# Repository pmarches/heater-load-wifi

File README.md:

What is this?
---

This repository contains code, drawings and schematics for a device that controls a heating element. This device will throttle the AC current of a device to the duty ratio configured via Wifi. 

The device has features that I could not find in commercial devices;

- Wifi connectivity, for both monitoring and control
- Victron Energy compatible drivers
- Internal temperature monitoring
- External temperature sensor

Use case
---
My use case is to heat water when I have superfluous solar energy. The victron driver knows when it is a good time to start pumping solar energy into heating water. 

Network operation
---
If the device has no Wifi access point configured, it will create one named. "heater load configuration AP". You can then point your web browser to http://10.0.0.1 to set the Wifi credentials and maximum connected load. Reboot the device to see it connect to the confgured AP. The device will advertise itself using MDNS, so you can use mdns-scan or Avahi broswer to get the IP information.

The device has a JSON API on the URL : http://esp32-XXXXXX.local/state the response and payload you can send it looks like this. The included web interface also uses this JSON endpoint.

```json
{
  "onPhaseCount": 1,
  "offPhaseCount": 2,
  "wifissid": "Landlubber",
  "loadWatts": 60,
  "targetWatts": 20,
  "triacTemperatureSensor": 34.63259125,
  "externalTemperatureSensor": null
}
```

The device also has a over the air update mechanism. You can point your browser to the web interface and upload a new firmware.

Victron Operation
---
TBD

Temperature calibration
----
Get the current known temperature from the UI, then record the "ratio" to the current reading. Apply that ratio to all readings. Default ratio is 1.0.

Electrical details
---
We use a TRIAC along with a TRIAC driver to select a certain count of phases from mains AC power.  This avoids the sharp voltage spikes typically associated with TRIACs driven by PWM. This should result in low electrical noise, and low heat loss from the TRIAC. 

The external temperature sensor is just a NTC 10K thermistor with a JST 2.0mm 2 pin connector. 

BOM
---
TBD

TODO
---
- [ ] Add temperature limit
- [ ] Test with higher loads
- [ ] Low power mode
- [ ] Autodetect AC frequency at boot time. Sanity checks for 60Hz
- [ ] Make compatible with 50HZ AC mains. Can it work on 220V ?
- [ ] Test on inverter
- [ ] Monitor TRIAC temperature. Shutdown if too hot.
- [ ] If cannot connect to AP after a few minutes, it should fallback to the temporary AP, to allow re-configuration.
- [ ] Secure configuration page with password.
- [ ] Reduce size of device with printed PCB. Modify enclosure

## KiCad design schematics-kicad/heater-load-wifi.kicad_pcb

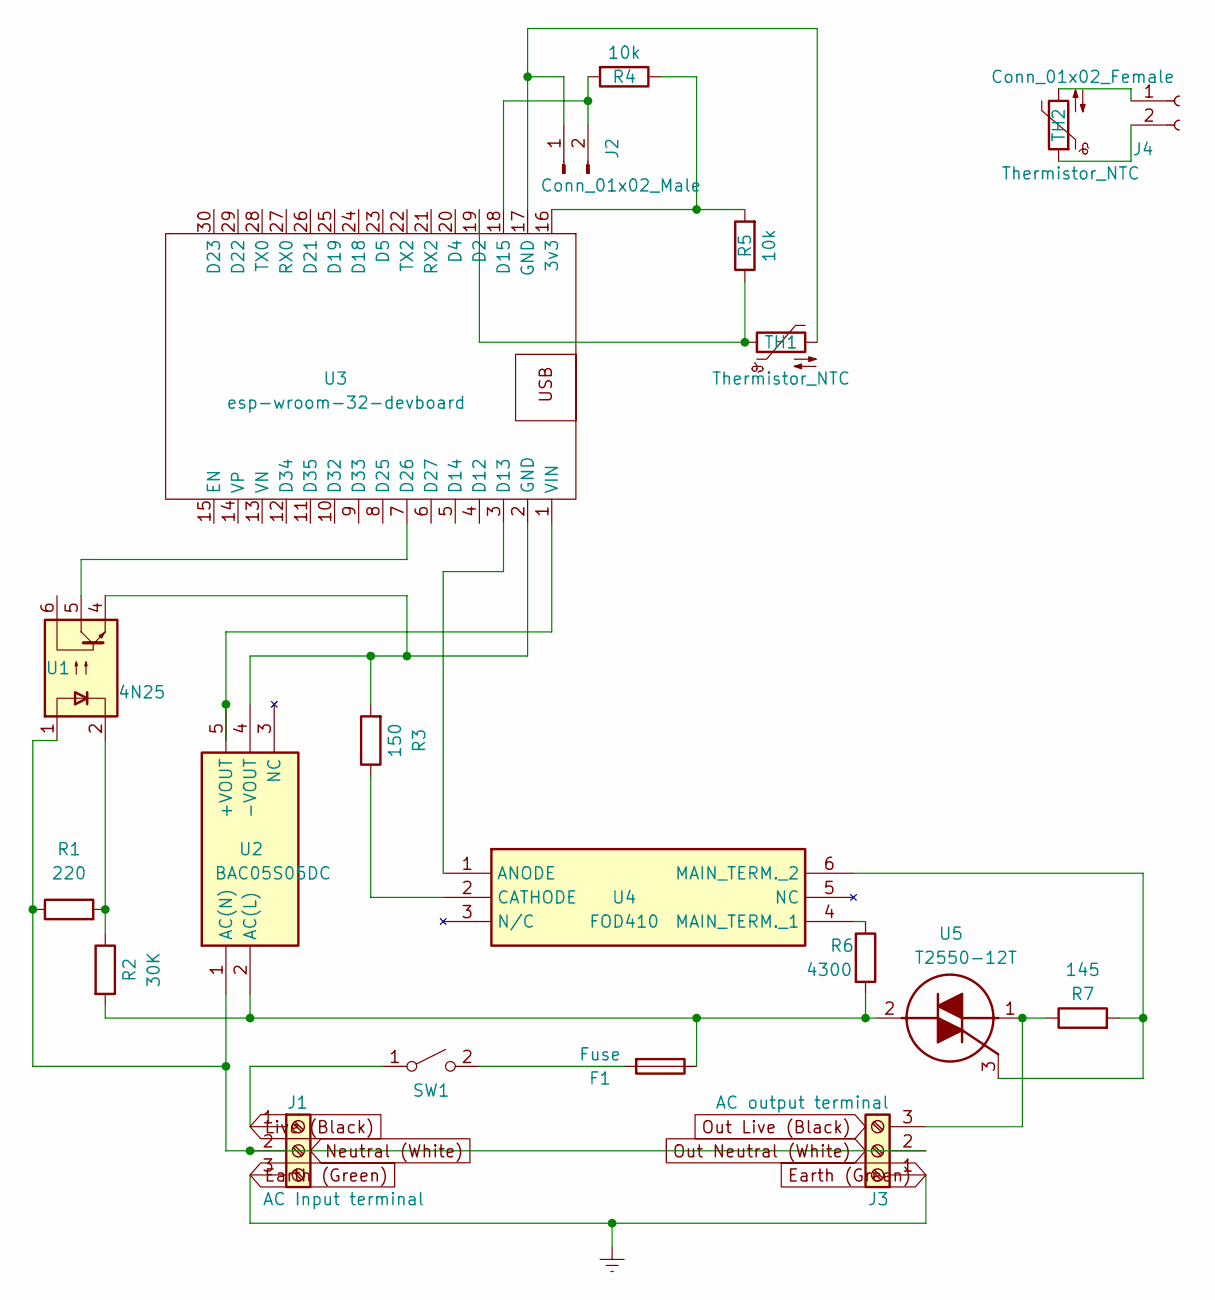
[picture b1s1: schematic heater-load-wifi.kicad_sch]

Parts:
F1: Fuse; Fuseholder_Blade_Mini_Keystone_3568
J1: AC Input terminal; TerminalBlock_Altech_AK300-3_P5.00mm
J2: Conn_01x02_Male; JST_JWPF_B02B-JWPF-SK-R_1x02_P2.00mm_Vertical
J3: AC output terminal; TerminalBlock_Altech_AK300-3_P5.00mm
J4: Conn_01x02_Female
R1: 220; R_Axial_DIN0411_L9.9mm_D3.6mm_P12.70mm_Horizontal
R2: 30K; R_Axial_DIN0411_L9.9mm_D3.6mm_P12.70mm_Horizontal
R3: 150; R_Axial_DIN0411_L9.9mm_D3.6mm_P12.70mm_Horizontal
R4, R5: 10k; R_Axial_DIN0411_L9.9mm_D3.6mm_P12.70mm_Horizontal
R6: 4300; R_Axial_DIN0411_L9.9mm_D3.6mm_P12.70mm_Horizontal
R7: 145; R_Axial_DIN0411_L9.9mm_D3.6mm_P12.70mm_Horizontal
SW1: SW_SPST; PinHeader_1x02_P2.54mm_Vertical
TH1, TH2: Thermistor_NTC; TestPoint_2Pads_Pitch2.54mm_Drill0.8mm
U1: 4N25; DIP-6_W7.62mm
U2: BAC05S05DC; Mouser Part Number 580-BAC05S05DC
U3: esp-wroom-32-devboard
U4: FOD410; DIP762W60P254L730H450Q6N; Mouser Part Number 512-FOD410
U5: T2550-12T; TO255P460X1020X2005-3P; Mouser Part Number 511-T2550-12T

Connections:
Earth (Green): J1.3, J3.1
Live (Black): J1.1, SW1.1 (A)
unnamed: F1.1, R2.2, R6.2, U2.2 (AC(L)), U5.2 (MT2)
unnamed: F1.2, SW1.2 (B)
unnamed: J2.1, TH1.2, U3.17 (GND)
unnamed: J2.2, R4.2, U3.18 (D15)
unnamed: J3.3, R7.1, U5.1 (MT1)
unnamed: J4.1, TH2.2
unnamed: J4.2, TH2.1
unnamed: R1.2, R2.1, U1.2
unnamed: R3.1, U4.2 (CATHODE)
unnamed: R3.2, U1.4, U2.4 (-VOUT), U3.2 (GND)
unnamed: R4.1, R5.2, U3.16 (3v3)
unnamed: R5.1, TH1.1, U3.19 (D2)
unnamed: R6.1, U4.4 (MAIN_TERM._1)
unnamed: R7.2, U4.6 (MAIN_TERM._2), U5.3 (G)
unnamed: U1.5, U3.7 (D26)
unnamed: U2.5 (+VOUT), U3.1 (VIN)
unnamed: U3.3 (D13), U4.1 (ANODE)
Neutral (White): J1.2, J3.2, R1.1, U1.1, U2.1 (AC(N))

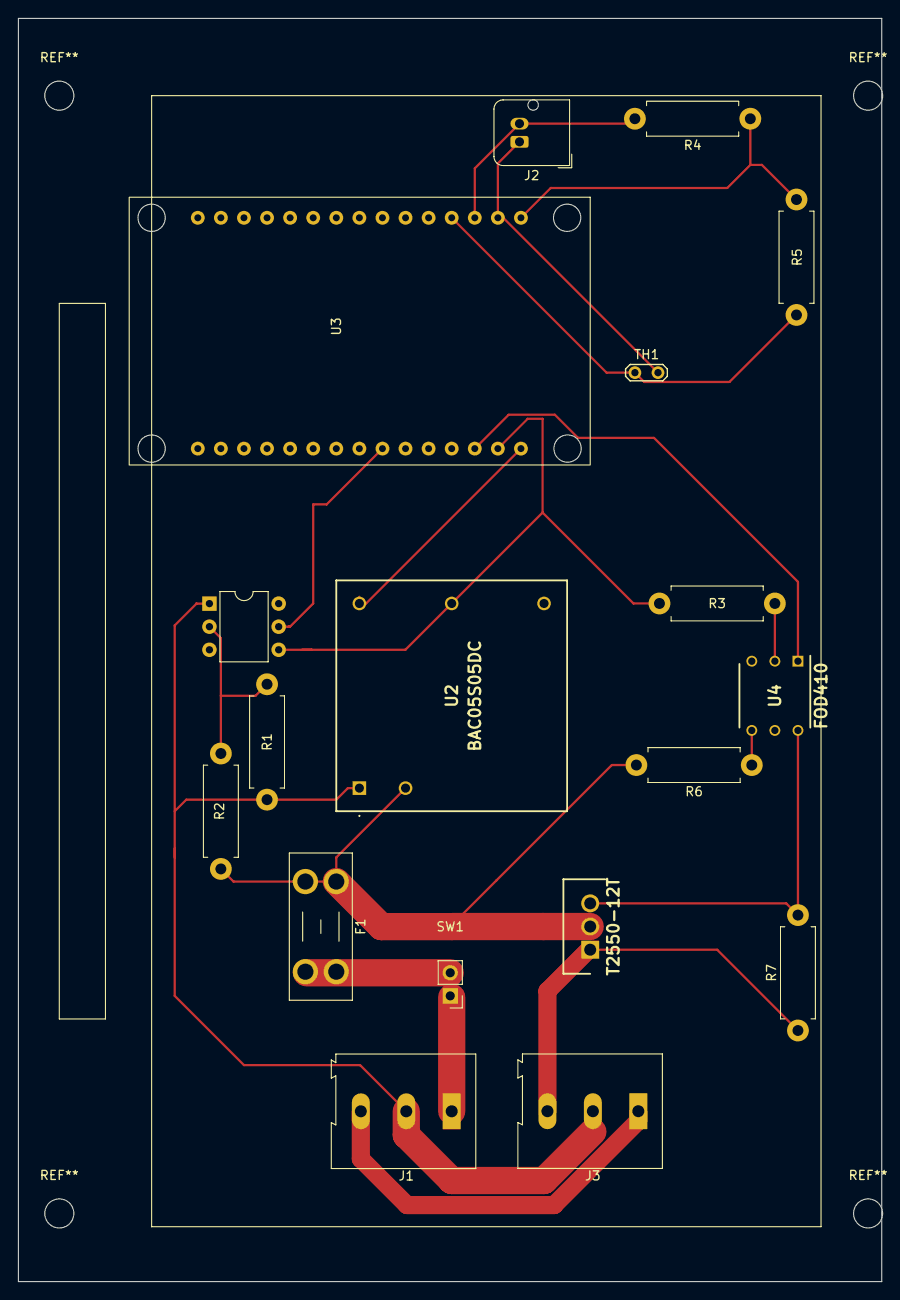
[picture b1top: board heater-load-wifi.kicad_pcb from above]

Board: 2 copper layers, 95.0 x 139.0 mm, 18 parts (0 on the bottom side), 18 nets.

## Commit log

2023-09-19 Media and readme
2023-09-19 Kicad schematics
2023-09-19 Arduino code
2023-09-20 Added footprint pic
2023-09-22 Added temperature compensation
2023-09-25 Added temperature limit
